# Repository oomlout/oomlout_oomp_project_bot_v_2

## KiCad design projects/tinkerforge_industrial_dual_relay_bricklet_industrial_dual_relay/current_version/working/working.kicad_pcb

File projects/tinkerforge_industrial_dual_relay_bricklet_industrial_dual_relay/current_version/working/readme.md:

# industrial_dual_relay_bricklet
 
## summary 
* id: tinkerforge_industrial_dual_relay_bricklet_industrial_dual_relay
* user: tinkerforge
* name: industrial_dual_relay_bricklet
* board: industrial_dual_relay
* repo: https://github.com/Tinkerforge/industrial-dual-relay-bricklet
* src_file_repo_kicad_pcb: hardware/industrial-dual-relay.kicad_pcb
* src_file_repo_kicad_pcb_link: https://github.com/Tinkerforge/industrial-dual-relay-bricklet/tree/master/hardware/industrial-dual-relay.kicad_pcb
* src_file_repo_kicad_sch: hardware/industrial-dual-relay.kicad_sch
* src_file_repo_kicad_sch_link: https://github.com/Tinkerforge/industrial-dual-relay-bricklet/tree/master/hardware/industrial-dual-relay.kicad_sch

* src_file_repo_sch: 
* src_file_repo_sch_link: https://github.com/Tinkerforge/industrial-dual-relay-bricklet/tree/master/
* full details link: https://github.com/oomlout/oomlout_oomp_project_bot_v_2/tree/main/projects/tinkerforge_industrial_dual_relay_bricklet_industrial_dual_relay/current_version/working

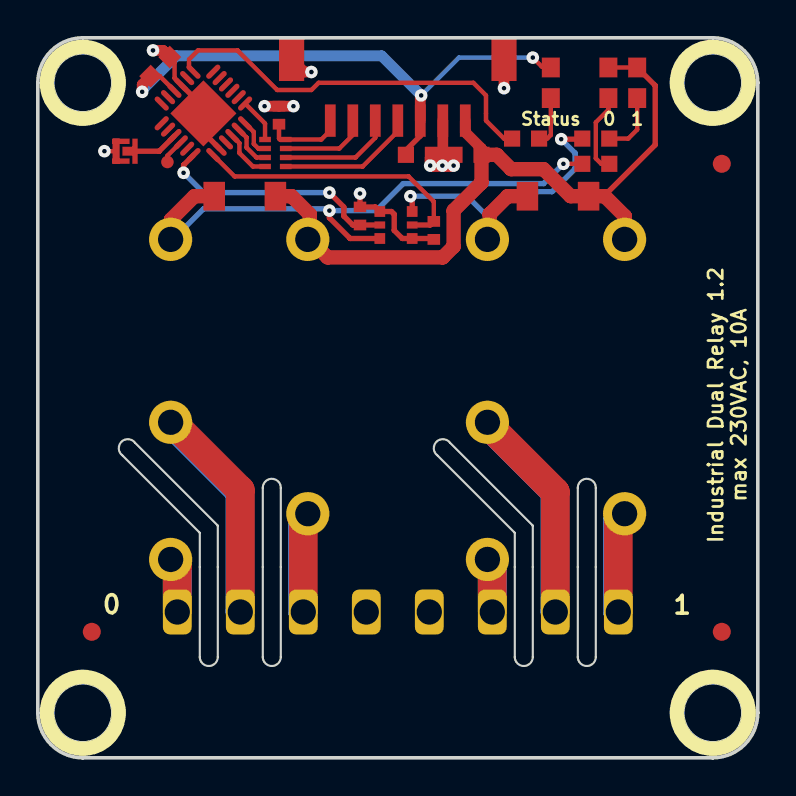
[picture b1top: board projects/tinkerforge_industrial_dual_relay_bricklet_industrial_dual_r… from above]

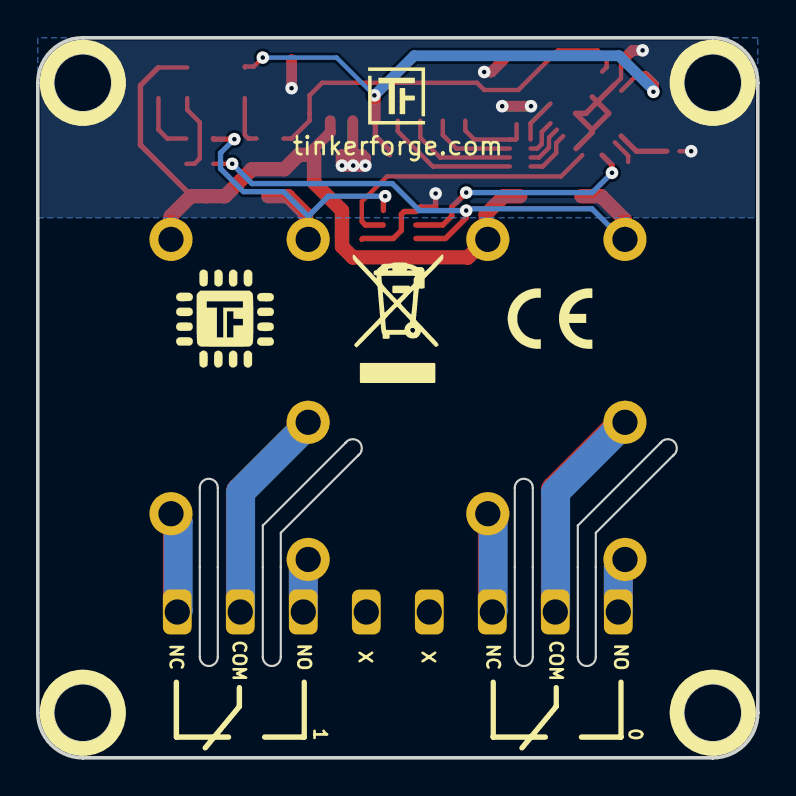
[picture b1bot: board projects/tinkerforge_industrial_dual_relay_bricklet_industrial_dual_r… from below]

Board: 2 copper layers, 40.0 x 40.0 mm, 31 parts (2 on the bottom side), 27 nets.

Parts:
C1, C3: 1uF; C0603F
C2: 220pF; C0402F
C4: 100nF; C0603F
D1, D2, D3: blue; D0603E
D4, D5: LL4148; MiniMelf
Fiducial_Mark: VAL**; Fiducial_Mark
Fiducial_Mark#2, Fiducial_Mark#3: VAL**; Fiducial_Mark
P1: CON-SENSOR2
P2: BOOT; SolderJumper
P3: CONN_8; OQ_8P_230V
P4: Debug; DEBUG_PAD
Q2, Q3: G5Q-1
R1, R2, R3: 1k; R0603F
R4, R5: 10k; R0402F
RP1: 82; 4X0402
U1: XMC1100; QFN24-4x4mm-0.5mm
U4, U5, U6: DRILL; DRILL_NP
VAL: CE_5mm
VAL#2: WEEE_7mm
locked: SSM6N7002KFU; SOT363

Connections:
+5V: C1.2, D2.1, D3.1, D4.2 (K), D5.2 (K), P1.1, Q2.A2, Q3.A2
GND: C1.1, C2.1, C3.1, C4.2, P1.2, P1.EP, P2.1, R4.1, R5.1, U1.9 (VSSP/VSS), U1.20 (P0.9_IO), U1.EXP (VSSP), locked.1, locked.4
unnamed: C2.2, P1.7, RP1.4
unnamed: D1.2, R1.2
unnamed: D2.2, R2.2
unnamed: D3.2, R3.2
unnamed: D4.1 (A), Q2.A1, R2.1, locked.6
unnamed: D5.1 (A), Q3.A1, R3.1, locked.3
unnamed: P1.4, RP1.1
unnamed: P1.5, RP1.2
unnamed: P1.6, RP1.3
unnamed: P2.2, U1.15 (P0.0_IO)
unnamed: P3.1, Q2.NO
unnamed: P3.2, Q2.COM
unnamed: P3.3, Q2.NC
unnamed: P3.6, Q3.NO
unnamed: P3.7, Q3.COM
unnamed: P3.8, Q3.NC
unnamed: P4.1, U1.16 (P0.5_IO)
unnamed: R1.1, U1.7 (P2.10_AIO)
RELAY0: R5.2, U1.19 (P0.8_IO), locked.5
RELAY1: R4.2, U1.18 (P0.7_IO), locked.2
S-CLK: RP1.7, U1.23 (P0.14_IO)
S-CS: RP1.8, U1.22 (P0.13_IO)
S-MISO: RP1.5, U1.1 (P2.0_AIO)
S-MOSI: RP1.6, U1.24 (P0.15_IO)
VCC: C3.2, C4.1, D1.1, P1.3, U1.10 (VDDP/VDD)

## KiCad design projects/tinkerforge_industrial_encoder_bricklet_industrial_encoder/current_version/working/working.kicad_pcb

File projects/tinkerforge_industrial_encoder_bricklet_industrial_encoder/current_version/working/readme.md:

# industrial_encoder_bricklet
 
## summary 
* id: tinkerforge_industrial_encoder_bricklet_industrial_encoder
* user: tinkerforge
* name: industrial_encoder_bricklet
* board: industrial_encoder
* repo: https://github.com/Tinkerforge/industrial-encoder-bricklet
* src_file_repo_kicad_pcb: hardware/industrial-encoder.kicad_pcb
* src_file_repo_kicad_pcb_link: https://github.com/Tinkerforge/industrial-encoder-bricklet/tree/master/hardware/industrial-encoder.kicad_pcb

* src_file_repo_sch: hardware/industrial-encoder.sch
* src_file_repo_sch_link: https://github.com/Tinkerforge/industrial-encoder-bricklet/tree/master/hardware/industrial-encoder.sch
* full details link: https://github.com/oomlout/oomlout_oomp_project_bot_v_2/tree/main/projects/tinkerforge_industrial_encoder_bricklet_industrial_encoder/current_version/working

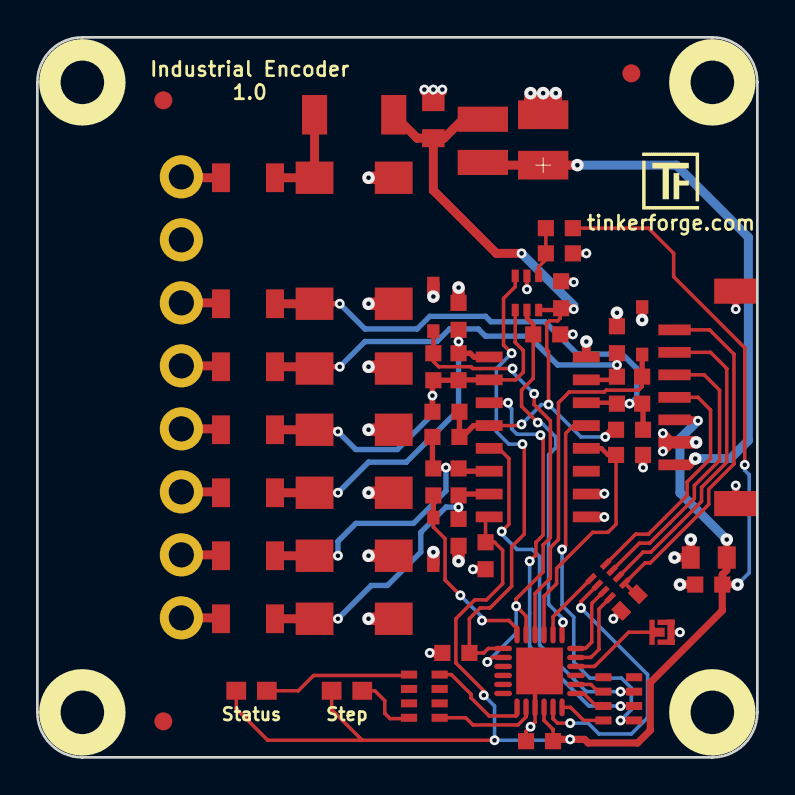
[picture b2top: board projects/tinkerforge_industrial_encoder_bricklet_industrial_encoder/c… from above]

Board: 2 copper layers, 40.0 x 40.0 mm, 63 parts (1 on the bottom side), 44 nets.

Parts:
C1: TBD; C0402E
C2: 10uF; C0805
C3, C5, C6: 100nF; C0603F
C4: 1uF; C0603F
C7: 100µF; 3528-21
C8: 10µF; C0805
D1: LED blue; D0603E
D2: LED green; D0603E
D3, D4, D11: ESD3V3D3B-TP; SOD-323
D5: PMEG6050; SOD-128
D6, D7, D8, D9, D10, D12, D13: SMAJ5.0CA; DO-214AC
Fiducial_Mark: VAL**; Fiducial_Mark
Fiducial_Mark#2, Fiducial_Mark#3: VAL**; Fiducial_Mark
L1: 6.8uH; WE-LQ-1210
P1: CON-SENSOR; CON-SENSOR2
P2: Boot; SolderJumper
P3: CONN_8; OQ_8P
R1, R2, R3, R4, R5, R8, R10, R11, R13, R22, R24: 1k; R0603F
R6, R7, R15: 100; R0603F
R9, R12, R23: 150; R0603F
R14, R16, R17, R18, R19, R20, R21: 10; R1206
RP1: TBD; 4X0402
RP2, RP3: 1k; 0603X4
U1: XMC1XXX24; QFN24-4x4mm-0.5mm
U2: OPA358; SC70-6
U3: ISL32173E; SOIC16
U4, U5, U6, U7: DRILL; DRILL_NP
VAL: CE_5mm

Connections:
+5V: C7.1, L1.1, P1.1
+5VA: C5.1, C8.2, D5.1, L1.2, R8.2, R11.2, R22.2, U2.6, U3.12
A-D: RP3.5, U3.5
A-T: D3.2, R6.1, U1.22
A/DAT: D7.1, R6.2, R8.1, R9.2, R16.2, U3.6
B-CLK: R1.2, U1.1, U2.3
B-CLK-EN: R2.2, U1.19, U2.5
B-D: RP3.6, U3.11
B-T: D4.2, R7.1, U1.2, U1.23
B/CLK: D9.1, R7.2, R11.1, R12.2, R18.2, U2.4, U3.10
EN-DIFF: R5.2, U1.21, U3.4
GND: C1.1, C2.1, C3.1, C4.1, C5.2, C6.2, C7.2, C8.1, D3.1, D4.1, D6.2, D7.2, D8.2, D9.2, D10.2, D11.1, D12.2, D13.2, P1.2, P1.EP, P2.1, P3.2, R1.1, R2.1, R4.1, R5.1, R10.1, R13.1, R24.1, U1.9, U1.EXP, U2.2, U3.1, U3.2, U3.8
I: D12.1, R15.2, R20.2, R22.1, R23.2, U3.14
I-D: RP3.7, U3.13
I-T: D11.2, R15.1, U1.24
unnamed: C1.2, P1.7, RP1.5
unnamed: D1.2, RP2.1
unnamed: D2.2, RP2.4
unnamed: D5.2, D6.1, R14.2
unnamed: P1.4, RP1.8
unnamed: P1.5, RP1.7
unnamed: P1.6, RP1.6
unnamed: P2.2, U1.16
unnamed: P3.1, R14.1
unnamed: P3.3, R16.1
unnamed: P3.4, R17.1
unnamed: P3.5, R18.1
unnamed: P3.6, R19.1
unnamed: P3.7, R20.1
unnamed: P3.8, R21.1
unnamed: R3.1, R4.2, U2.1
unnamed: RP2.5, U1.8
unnamed: RP2.8, U1.7
unnamed: RP3.2, U1.14
unnamed: RP3.3, U1.13
unnamed: RP3.4, U1.12
S-CLK: RP1.2, U1.11
S-CS: RP1.1, U1.20
S-MISO: RP1.4, U1.17
S-MOSI: RP1.3, U1.18
VCC: C2.2, C3.2, C4.2, C6.1, D1.1, D2.1, P1.3, R3.2, U1.10, U3.16
~A: D8.1, R9.1, R10.2, R17.2, U3.7
~B: D10.1, R12.1, R13.2, R19.2, U3.9
~I: D13.1, R21.2, R23.1, R24.2, U3.15

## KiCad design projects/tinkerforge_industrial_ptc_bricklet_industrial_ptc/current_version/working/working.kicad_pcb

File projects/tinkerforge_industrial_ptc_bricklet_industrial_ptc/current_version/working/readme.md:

# industrial_ptc_bricklet
 
## summary 
* id: tinkerforge_industrial_ptc_bricklet_industrial_ptc
* user: tinkerforge
* name: industrial_ptc_bricklet
* board: industrial_ptc
* repo: https://github.com/Tinkerforge/industrial-ptc-bricklet
* src_file_repo_kicad_pcb: hardware/industrial-ptc.kicad_pcb
* src_file_repo_kicad_pcb_link: https://github.com/Tinkerforge/industrial-ptc-bricklet/tree/master/hardware/industrial-ptc.kicad_pcb
* src_file_repo_kicad_sch: hardware/industrial-ptc.kicad_sch
* src_file_repo_kicad_sch_link: https://github.com/Tinkerforge/industrial-ptc-bricklet/tree/master/hardware/industrial-ptc.kicad_sch

* src_file_repo_sch: 
* src_file_repo_sch_link: https://github.com/Tinkerforge/industrial-ptc-bricklet/tree/master/
* full details link: https://github.com/oomlout/oomlout_oomp_project_bot_v_2/tree/main/projects/tinkerforge_industrial_ptc_bricklet_industrial_ptc/current_version/working

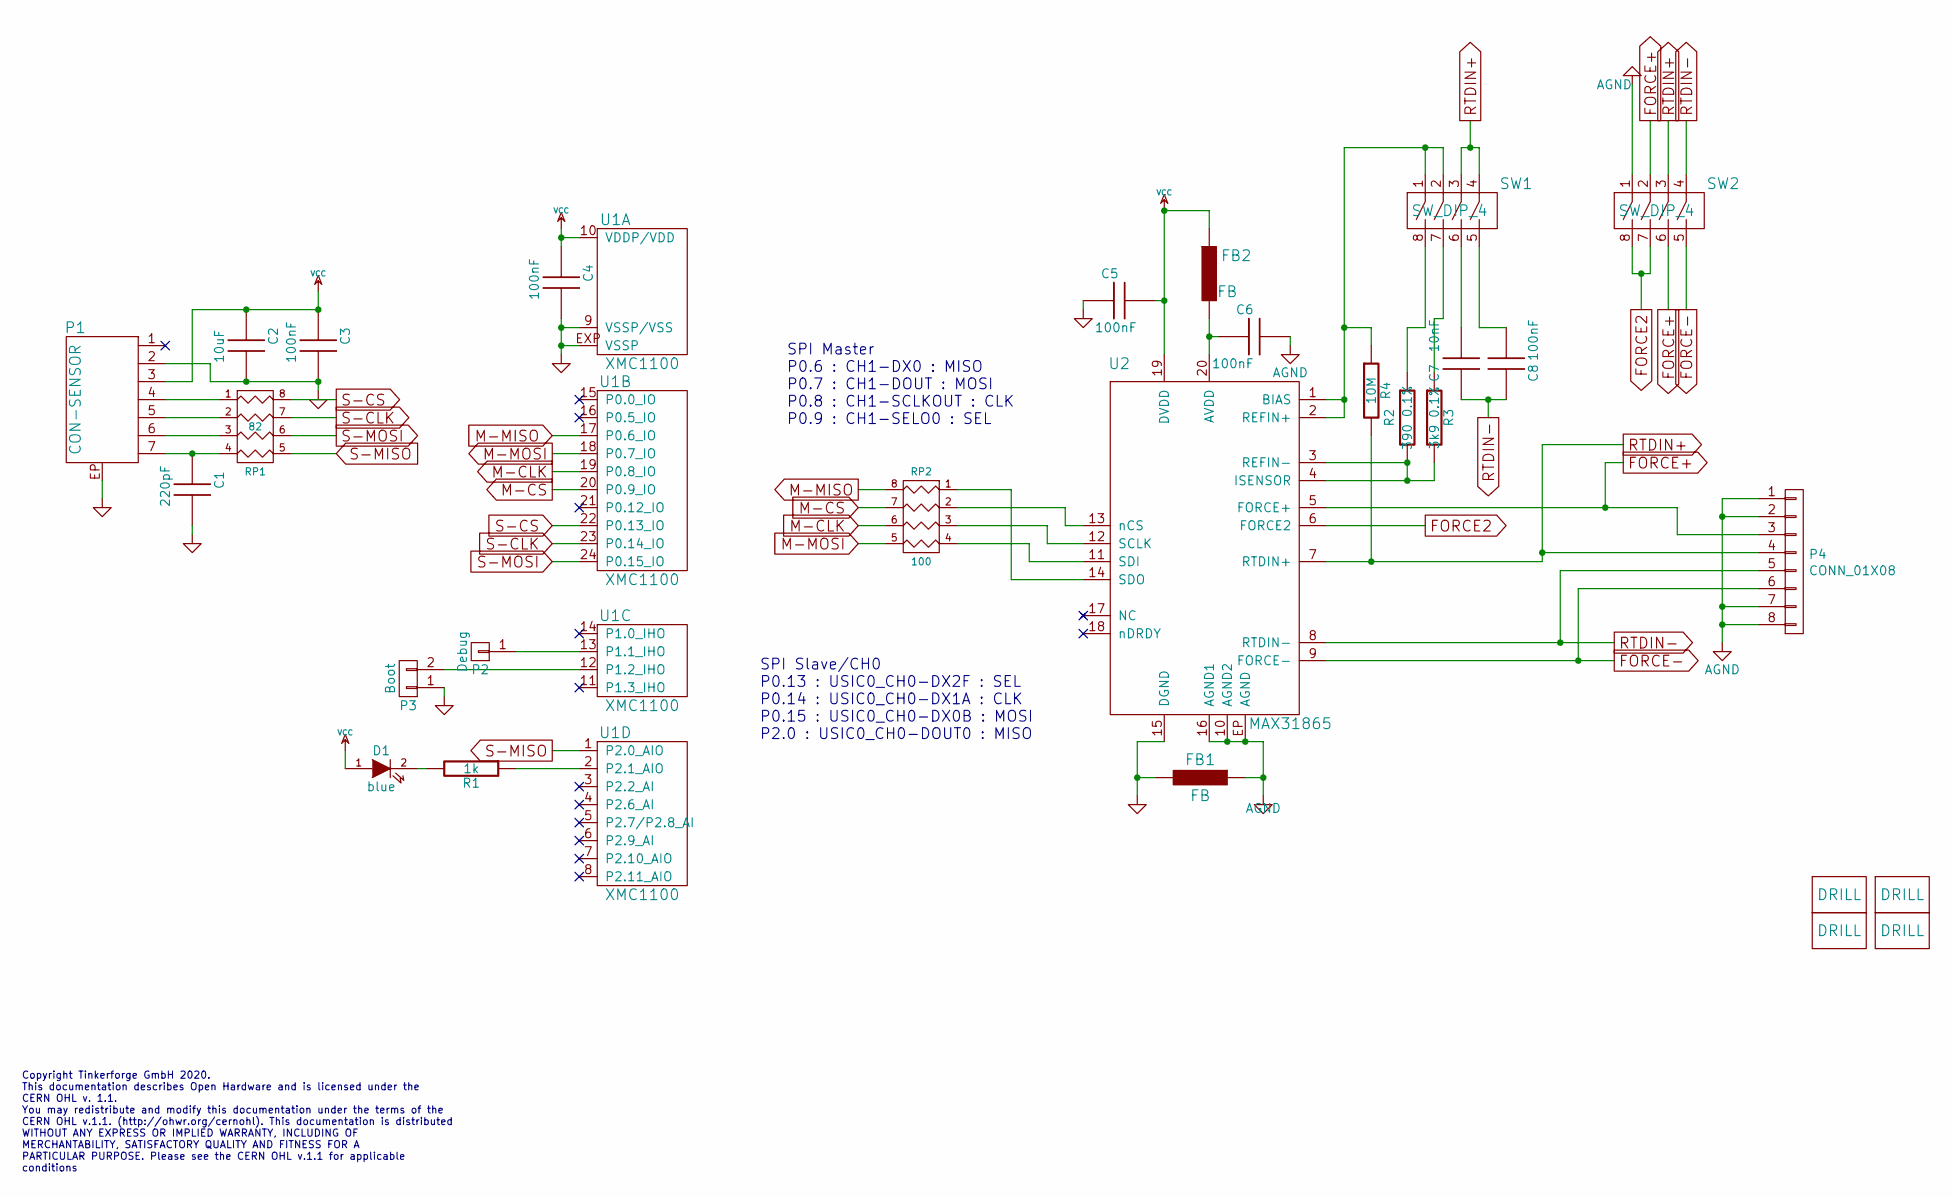
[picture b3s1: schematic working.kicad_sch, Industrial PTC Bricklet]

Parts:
C1: 220pF; C0402F
C2: 10uF; C0805
C3, C4, C5, C6, C8: 100nF; C0603F
C7: 10nF; C0603F
D1: blue; D0603F
FB1, FB2: FB; R0603F
P1: CON-SENSOR; CON-SENSOR2
P2: Debug; DEBUG_PAD
P3: Boot; SolderJumper
P4: CONN_01X08; OQ_8P
R1: 1k; R0603F
R2: 390 0.1%; R0603F
R3: 3k9 0.1%; R0603F
R4: 10M; R0603F
RP1: 82; 4X0402
RP2: 100; 0603X4
SW1, SW2: SW_DIP_4; SW_DIP_4_THT
U1: XMC1100; QFN24-4x4mm-0.5mm
U2: MAX31865; QFN-20-5x5
U3, U4, U5, U6: DRILL; DRILL_NP

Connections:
AGND: C6.2, FB1.1, P4.1, P4.2, P4.7, P4.8, SW2.1, U2.10 (AGND2), U2.16 (AGND1), U2.EP (AGND)
FORCE2: SW2.7, SW2.8, U2.6 (FORCE2)
FORCE+: P4.3, SW2.2, SW2.6, U2.5 (FORCE+)
FORCE-: P4.6, SW2.5, U2.9 (FORCE-)
GND: C1.2, C2.2, C3.2, C4.2, C5.1, FB1.2, P1.2, P1.EP, P3.1, U1.9 (VSSP/VSS), U1.EXP (VSSP), U2.15 (DGND)
M-CLK: RP2.6 (R3), U1.19 (P0.8_IO)
M-CS: RP2.7 (R2), U1.20 (P0.9_IO)
M-MISO: RP2.8 (R1), U1.17 (P0.6_IO)
M-MOSI: RP2.5 (R4), U1.18 (P0.7_IO)
unnamed: C1.1, P1.7, RP1.4
unnamed: C6.1, FB2.2, U2.20 (AVDD)
unnamed: C7.2, SW1.6
unnamed: C8.2, SW1.5
unnamed: D1.2 (K), R1.2
unnamed: P1.4, RP1.1
unnamed: P1.5, RP1.2
unnamed: P1.6, RP1.3
unnamed: P2.1, U1.13 (P1.1_IHO)
unnamed: P3.2, U1.12 (P1.2_IHO)
unnamed: R1.1, U1.2 (P2.1_AIO)
unnamed: R2.1, SW1.8
unnamed: R2.2, R3.2, U2.3 (REFIN-), U2.4 (ISENSOR)
unnamed: R3.1, SW1.7
unnamed: R4.1, SW1.1, SW1.2, U2.1 (BIAS), U2.2 (REFIN+)
unnamed: RP2.1, U2.14 (SDO)
unnamed: RP2.2, U2.13 (nCS)
unnamed: RP2.3, U2.12 (SCLK)
unnamed: RP2.4, U2.11 (SDI)
RTDIN+: P4.4, R4.2, SW1.3, SW1.4, SW2.3, U2.7 (RTDIN+)
RTDIN-: C7.1, C8.1, P4.5, SW2.4, U2.8 (RTDIN-)
S-CLK: RP1.7 (R2), U1.23 (P0.14_IO)
S-CS: RP1.8 (R1), U1.22 (P0.13_IO)
S-MISO: RP1.5 (R4), U1.1 (P2.0_AIO)
S-MOSI: RP1.6 (R3), U1.24 (P0.15_IO)
VCC: C2.1, C3.1, C4.1, C5.2, D1.1 (A), FB2.1, P1.3, U1.10 (VDDP/VDD), U2.19 (DVDD)

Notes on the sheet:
SPI Master P0.6 : CH1-DX0 : MISO P0.7 : CH1-DOUT : MOSI P0.8 : CH1-SCLKOUT : CLK P0.9 : CH1-SELO0 : SEL
Copyright Tinkerforge GmbH 2020. This documentation describes Open Hardware and is licensed under the CERN OHL v. 1.1. You may redistribute and modify this documentation under the terms of the CERN OHL v.1.1. (http://ohwr.org/cernohl). This documentation is distributed WITHOUT ANY EXPRESS OR IMPLIE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
SPI Slave/CH0 P0.13 : USIC0_CH0-DX2F : SEL P0.14 : USIC0_CH0-DX1A : CLK P0.15 : USIC0_CH0-DX0B : MOSI P2.0 : USIC0_CH0-DOUT0 : MISO

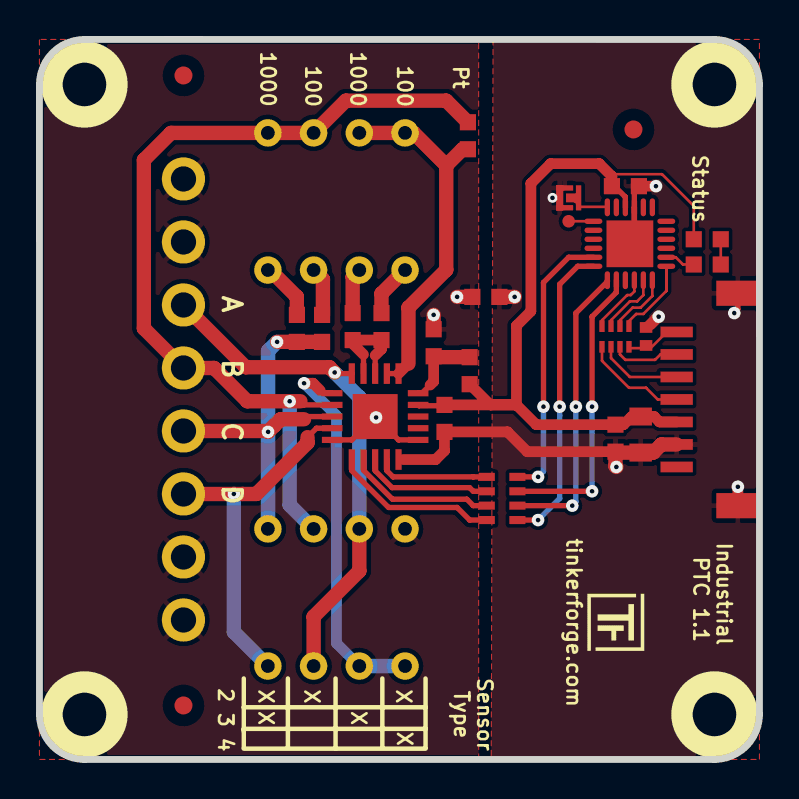
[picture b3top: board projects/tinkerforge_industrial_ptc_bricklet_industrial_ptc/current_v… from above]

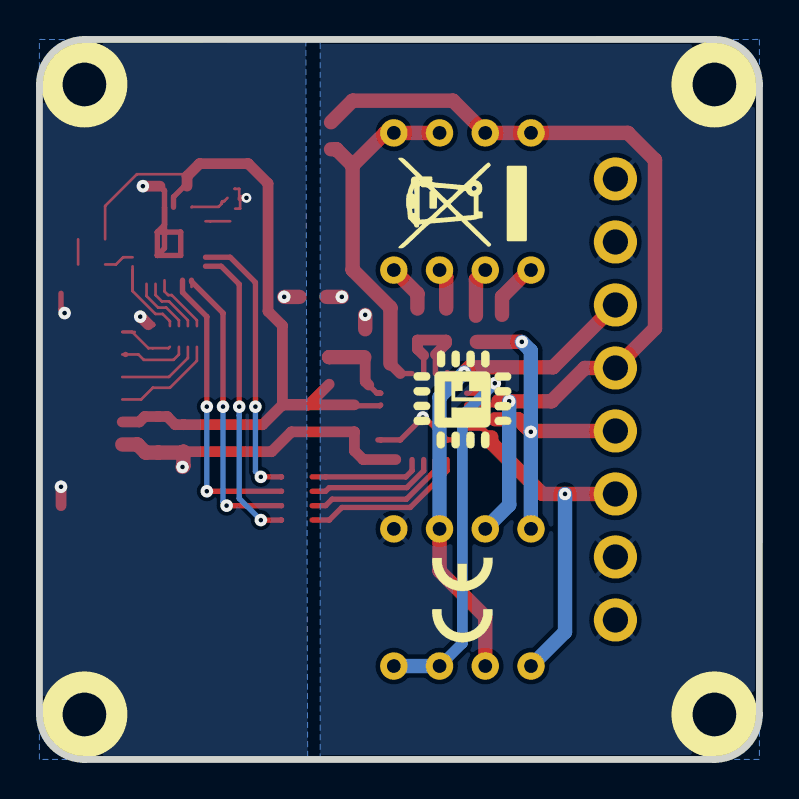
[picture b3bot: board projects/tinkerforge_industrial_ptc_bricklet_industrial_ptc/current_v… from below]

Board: 2 copper layers, 40.0 x 40.0 mm, 34 parts (2 on the bottom side), 35 nets.

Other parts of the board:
Fiducial_Mark: VAL**; Fiducial_Mark
Fiducial_Mark#2, Fiducial_Mark#3: VAL**; Fiducial_Mark
VAL: CE_5mm
VAL#2: WEEE_7mm

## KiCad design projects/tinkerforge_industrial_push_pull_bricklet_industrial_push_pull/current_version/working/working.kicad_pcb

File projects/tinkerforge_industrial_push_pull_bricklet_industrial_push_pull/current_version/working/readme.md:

# industrial_push_pull_bricklet
 
## summary 
* id: tinkerforge_industrial_push_pull_bricklet_industrial_push_pull
* user: tinkerforge
* name: industrial_push_pull_bricklet
* board: industrial_push_pull
* repo: https://github.com/Tinkerforge/industrial-push-pull-bricklet
* src_file_repo_kicad_pcb: hardware/industrial-push-pull.kicad_pcb
* src_file_repo_kicad_pcb_link: https://github.com/Tinkerforge/industrial-push-pull-bricklet/tree/master/hardware/industrial-push-pull.kicad_pcb

* src_file_repo_sch: hardware/industrial-push-pull.sch
* src_file_repo_sch_link: https://github.com/Tinkerforge/industrial-push-pull-bricklet/tree/master/hardware/industrial-push-pull.sch
* full details link: https://github.com/oomlout/oomlout_oomp_project_bot_v_2/tree/main/projects/tinkerforge_industrial_push_pull_bricklet_industrial_push_pull/current_version/working

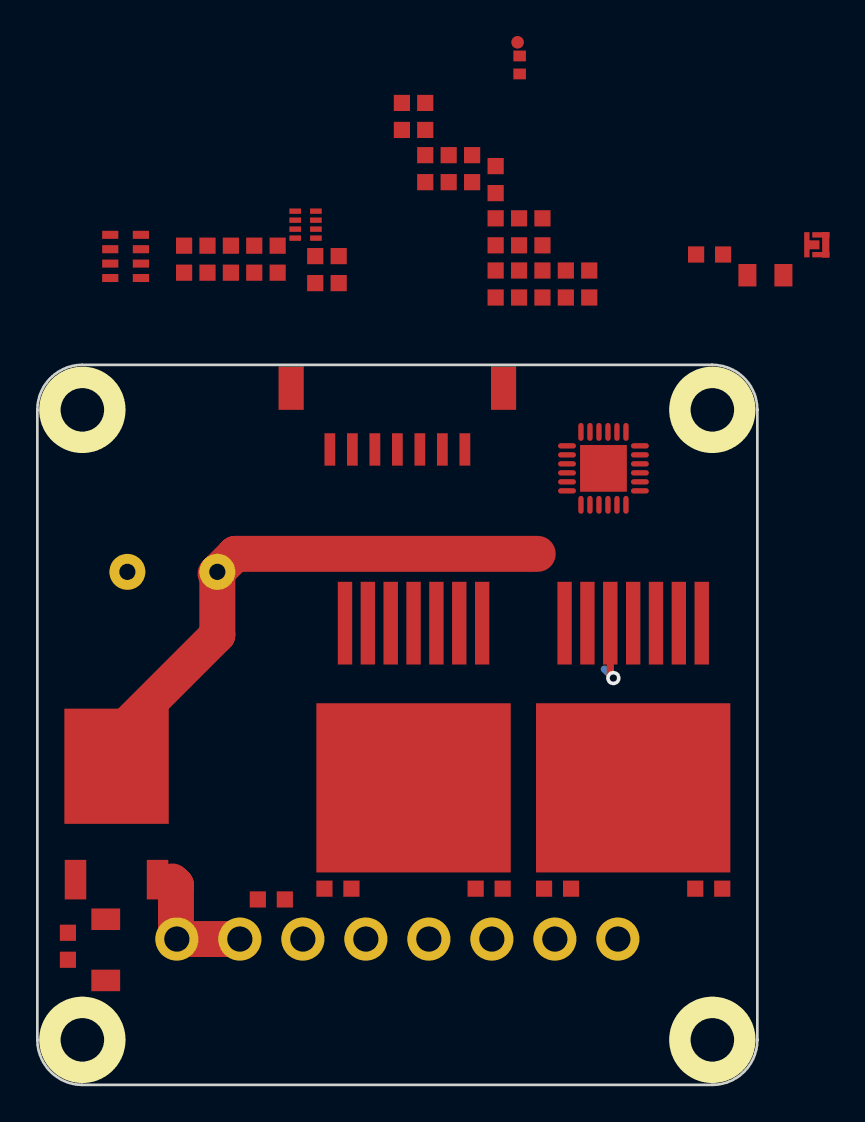
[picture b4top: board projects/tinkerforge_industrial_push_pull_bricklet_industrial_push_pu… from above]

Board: 2 copper layers, 40.0 x 40.0 mm, 46 parts (0 on the bottom side), 37 nets.

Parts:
10k1: R; R0603F
C1, C4, C6, C7, C8: 100nF; C0603F
C2: 220pF; C0402F
C3: 10uF; C0805
C5: 1nF; C0603F
C9: 1000uF 35V; ELKO_RAD_12
C10, C11, C12: 100nF 100V; C0603F
C13, C14, C15, C16: 220nF 100V; C0603F
D1: blue STATUS; D0603F
D2: 10V; MiniMelf
D3: red FAIL; D0603F
D4: green CH1; D0603F
D5: green CH2; D0603F
P1: CON-SENSOR; CON-SENSOR2
P2: Digital Output; OQ_8P
P3: Debug; DEBUG_PAD
P4: Boot; SolderJumper
Q1: MOSFET; TO-252-3
R1: 1k; R0603F
R2: 510; C0603F
R3, R4: 510; R0603F
R6, R7, R8, R9, R10: 10k; R0603F
R11: 91k; R0603F
RP1: 1k; 4X0603
RP2: 82; 4X0402
U1: XMC1100; QFN24-4x4mm-0.5mm
U2, U3: IFX007T; TO263-7
U6, U7, U8, U9: DRILL; DRILL_NP

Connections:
3V3: C1.1, C3.1, C4.1, D1.1, D3.1, D4.1, D5.1, P1.3, U1.10
+VSW: C9.1, C10.1, C11.1, C13.1, C15.1, D2.2, Q1.D, R11.1, U2.7, U3.7
GND: 10k1.2, C1.2, C2.2, C3.2, C4.2, C5.2, C6.2, C7.2, C8.2, C9.2, C10.2, C11.2, C12.2, C14.2, C16.2, P1.2, P1.EP, P2.3, P2.4, P4.1, Q1.G, R1.2, R2.2, R3.2, R4.2, R10.2, U1.9, U1.EXP, U2.1, U3.1
IN1: R6.2, U1.15
IN2: R8.2, U1.16
INH: R7.2, R9.2, U1.17
IS1: C5.1, R1.1, U1.14, U2.6
IS2: C7.1, R3.1, U1.13, U3.6
unnamed: 10k1.1, D2.1
unnamed: C2.1, P1.7, RP2.4
unnamed: C6.1, R2.1, U2.5
unnamed: C8.1, R4.1, U3.5
unnamed: C12.1, P2.1, P2.2, Q1.S
unnamed: C13.2, C14.1, P2.5, P2.6, U2.4, U2.8
unnamed: C15.2, C16.1, P2.7, P2.8, U3.4, U3.8
unnamed: D1.2, RP1.4
unnamed: D3.2, RP1.1
unnamed: D4.2, RP1.2
unnamed: D5.2, RP1.3
unnamed: P1.4, RP2.1
unnamed: P1.5, RP2.2
unnamed: P1.6, RP2.3
unnamed: P3.1, U1.19
unnamed: P4.2, U1.18
unnamed: R6.1, U2.2
unnamed: R7.1, U2.3
unnamed: R8.1, U3.2
unnamed: R9.1, U3.3
unnamed: RP1.5, U1.7
unnamed: RP1.6, U1.11
unnamed: RP1.7, U1.12
unnamed: RP1.8, U1.21
S-CLK: RP2.7, U1.23
S-CS: RP2.8, U1.22
S-MISO: RP2.5, U1.1
S-MOSI: RP2.6, U1.24
VIN: R10.1, R11.2, U1.2

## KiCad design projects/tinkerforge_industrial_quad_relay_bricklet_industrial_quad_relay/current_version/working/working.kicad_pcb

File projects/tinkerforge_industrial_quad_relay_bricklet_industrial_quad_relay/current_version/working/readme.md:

# industrial_quad_relay_bricklet
 
## summary 
* id: tinkerforge_industrial_quad_relay_bricklet_industrial_quad_relay
* user: tinkerforge
* name: industrial_quad_relay_bricklet
* board: industrial_quad_relay
* repo: https://github.com/Tinkerforge/industrial-quad-relay-bricklet
* src_file_repo_kicad_pcb: hardware/industrial-quad-relay.kicad_pcb
* src_file_repo_kicad_pcb_link: https://github.com/Tinkerforge/industrial-quad-relay-bricklet/tree/master/hardware/industrial-quad-relay.kicad_pcb

* src_file_repo_sch: hardware/industrial-quad-relay.sch
* src_file_repo_sch_link: https://github.com/Tinkerforge/industrial-quad-relay-bricklet/tree/master/hardware/industrial-quad-relay.sch
* full details link: https://github.com/oomlout/oomlout_oomp_project_bot_v_2/tree/main/projects/tinkerforge_industrial_quad_relay_bricklet_industrial_quad_relay/current_version/working

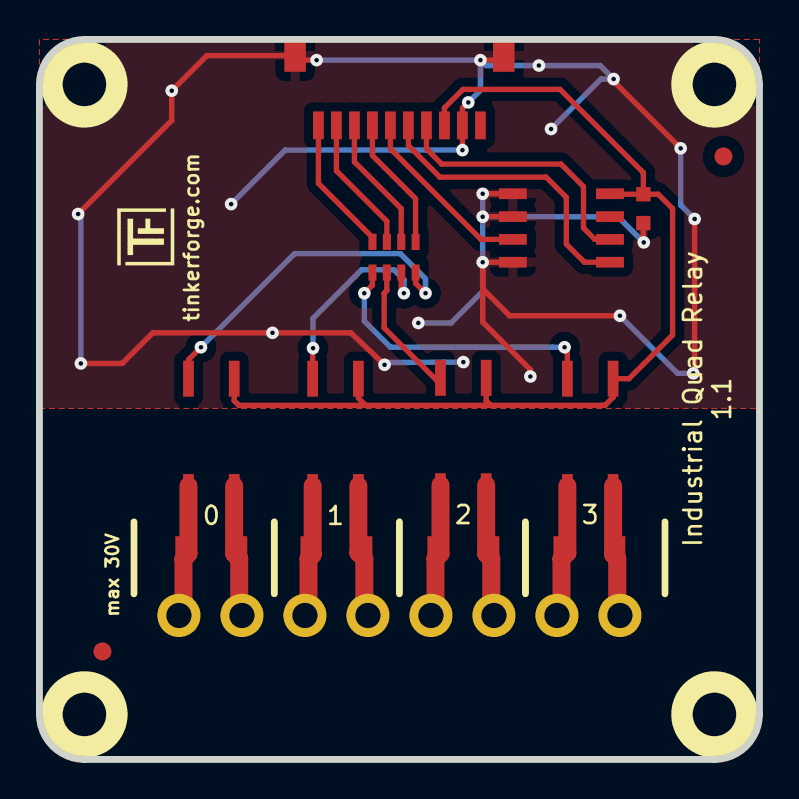
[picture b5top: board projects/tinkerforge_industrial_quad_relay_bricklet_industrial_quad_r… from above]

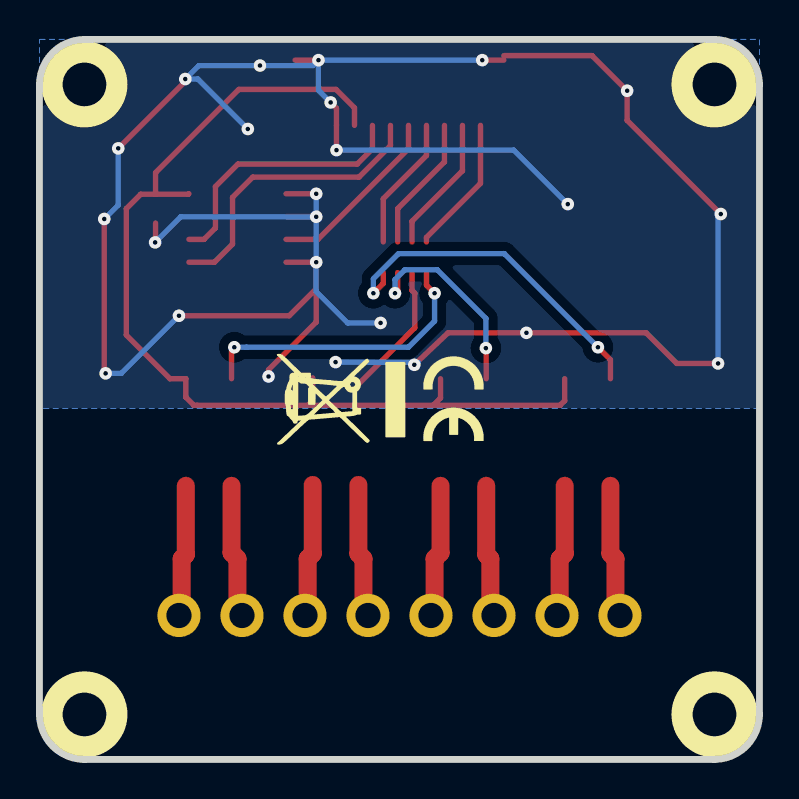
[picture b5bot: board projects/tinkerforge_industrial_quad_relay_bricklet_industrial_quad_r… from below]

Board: 2 copper layers, 40.0 x 40.0 mm, 21 parts (2 on the bottom side), 21 nets.

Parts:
C1: 100nF; C0603
Fiducial_Mark: VAL**; Fiducial_Mark
Fiducial_Mark#2: VAL**; Fiducial_Mark
P1: CON-SENSOR
P2: Digital Output; OQ_8P
R1, R2, R3, R4: VJ13PC0300KBA; R1210
RP1: 1k; 0603X4
U1: M24C64; SOIC8
U2, U3, U4, U5: CPC1020N; SOP4-WIDE
U6, U7, U8, U9: DRILL; DRILL_NP
VAL: WEEE_7mm
VAL#2: CE_5mm

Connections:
3V3: C1.1, P1.3, U1.8, U2.1, U3.1, U4.1, U5.1
GND: C1.2, P1.2, P1.EP, U1.1, U1.2, U1.4
unnamed: P1.4, U1.6
unnamed: P1.5, U1.5
unnamed: P1.6, U1.3
unnamed: P2.1, R1.1, U2.3
unnamed: P2.2, R1.2, U2.4
unnamed: P2.3, R2.1, U3.3
unnamed: P2.4, R2.2, U3.4
unnamed: P2.5, R3.1, U4.3
unnamed: P2.6, R3.2, U4.4
unnamed: P2.7, R4.1, U5.3
unnamed: P2.8, R4.2, U5.4
unnamed: RP1.5, U5.2
unnamed: RP1.6, U4.2
unnamed: RP1.7, U3.2
unnamed: RP1.8, U2.2
OUTPUT1: P1.7, RP1.1
OUTPUT2: P1.8, RP1.2
OUTPUT3: P1.9, RP1.3
OUTPUT4: P1.10, RP1.4

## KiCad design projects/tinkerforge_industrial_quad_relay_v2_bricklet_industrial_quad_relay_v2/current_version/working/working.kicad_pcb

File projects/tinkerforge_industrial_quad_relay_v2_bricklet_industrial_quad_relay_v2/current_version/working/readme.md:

# industrial_quad_relay_v2_bricklet
 
## summary 
* id: tinkerforge_industrial_quad_relay_v2_bricklet_industrial_quad_relay_v2
* user: tinkerforge
* name: industrial_quad_relay_v2_bricklet
* board: industrial_quad_relay_v2
* repo: https://github.com/Tinkerforge/industrial-quad-relay-v2-bricklet
* src_file_repo_kicad_pcb: hardware/industrial-quad-relay-v2.kicad_pcb
* src_file_repo_kicad_pcb_link: https://github.com/Tinkerforge/industrial-quad-relay-v2-bricklet/tree/master/hardware/industrial-quad-relay-v2.kicad_pcb
* src_file_repo_kicad_sch: hardware/industrial-quad-relay-v2.kicad_sch
* src_file_repo_kicad_sch_link: https://github.com/Tinkerforge/industrial-quad-relay-v2-bricklet/tree/master/hardware/industrial-quad-relay-v2.kicad_sch

* src_file_repo_sch: 
* src_file_repo_sch_link: https://github.com/Tinkerforge/industrial-quad-relay-v2-bricklet/tree/master/
* full details link: https://github.com/oomlout/oomlout_oomp_project_bot_v_2/tree/main/projects/tinkerforge_industrial_quad_relay_v2_bricklet_industrial_quad_relay_v2/current_version/working

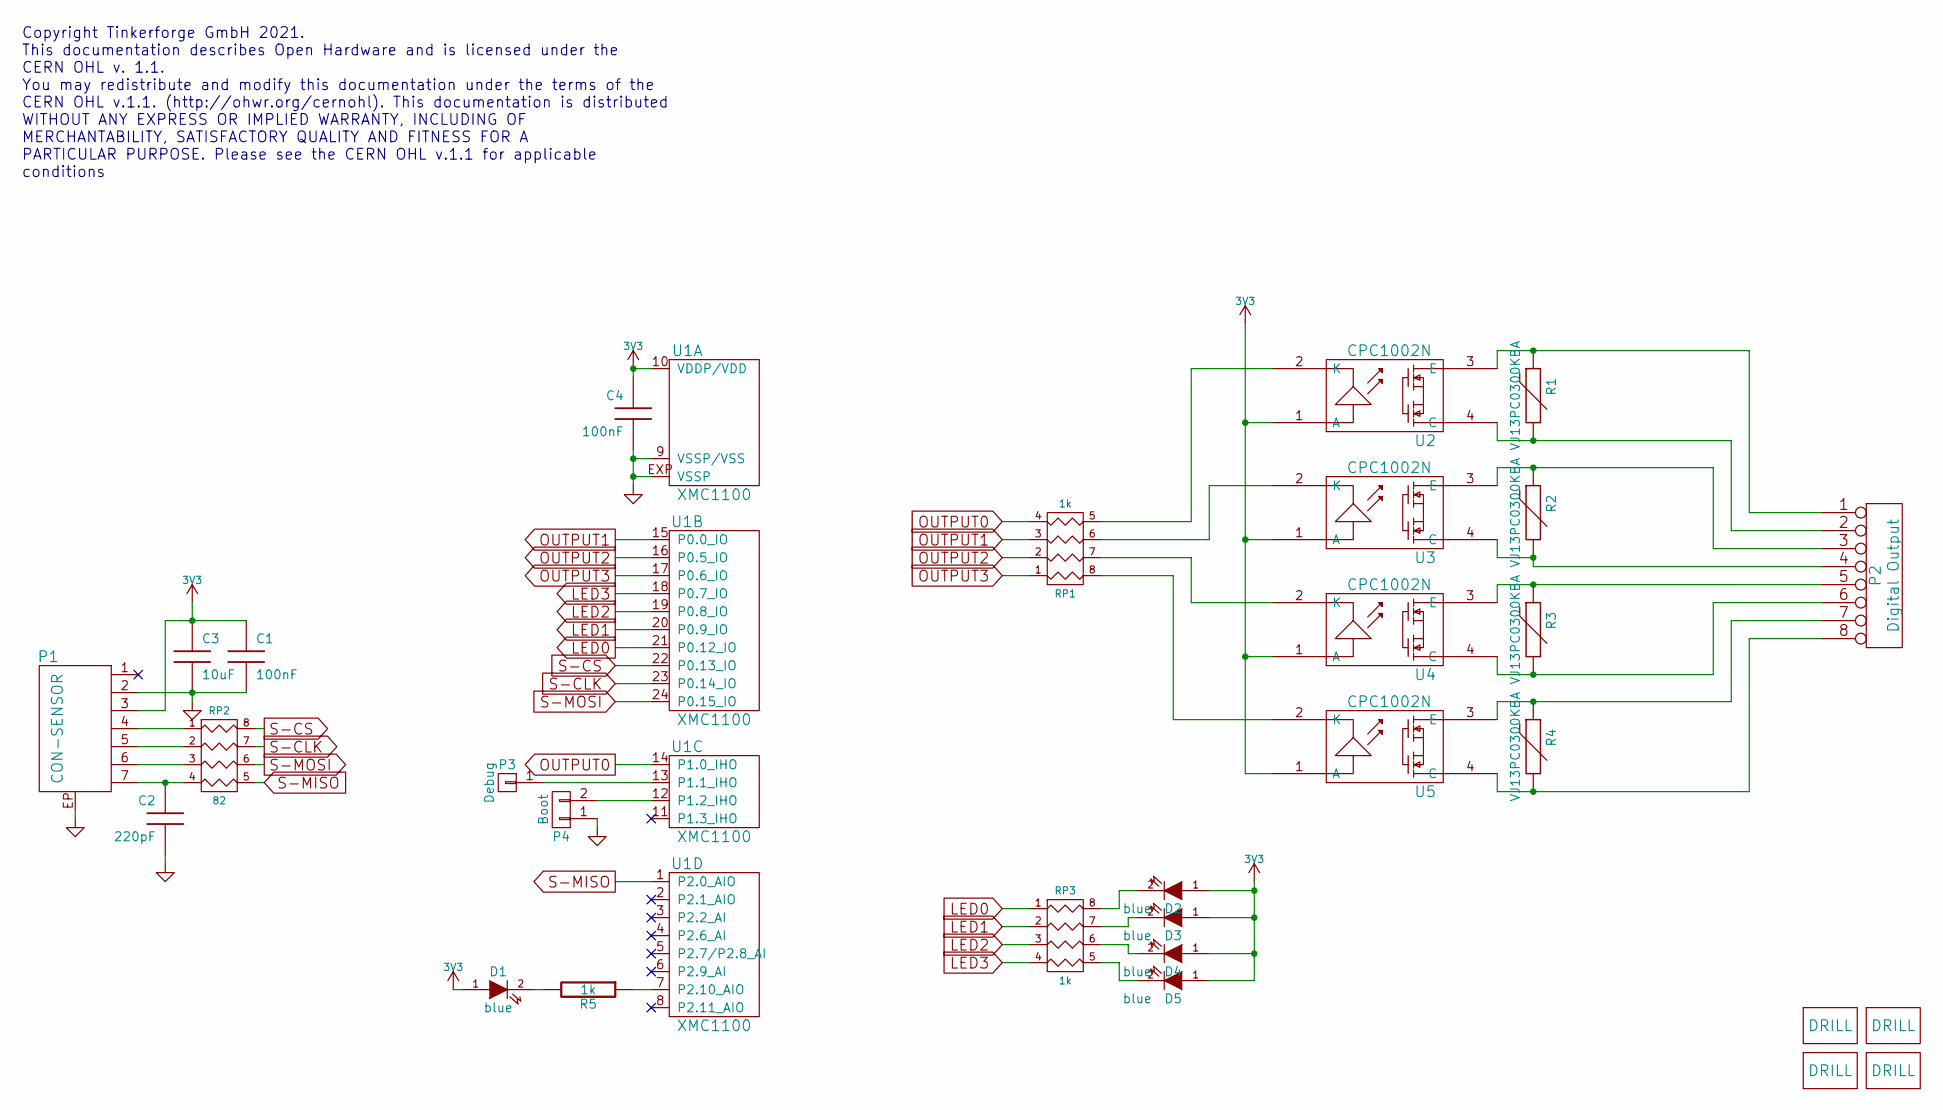
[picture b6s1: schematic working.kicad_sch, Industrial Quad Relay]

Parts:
C1, C4: 100nF; C0603F
C2: 220pF; C0402F
C3: 10uF; C0805
D1, D2, D3, D4, D5: blue; D0603F
P1: CON-SENSOR; CON-SENSOR2
P2: Digital Output; OQ_8P
P3: Debug; DEBUG_PAD
P4: Boot; SolderJumper
R1, R2, R3, R4: VJ13PC0300KBA; R1210
R5: 1k; R0603F
RP1, RP3: 1k; 0603X4
RP2: 82; 4X0402
U1: XMC1100; QFN24-4x4mm-0.5mm
U2, U3, U4, U5: CPC1002N; SOP4-WIDE
U6, U7, U8, U9: DRILL; DRILL_NP

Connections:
3V3: C1.1, C3.1, C4.1, D1.1 (A), D2.1 (A), D3.1 (A), D4.1 (A), D5.1 (A), P1.3, U1.10 (VDDP/VDD), U2.1 (A), U3.1 (A), U4.1 (A), U5.1 (A)
GND: C1.2, C2.2, C3.2, C4.2, P1.2, P1.EP, P4.1, U1.9 (VSSP/VSS), U1.EXP (VSSP)
LED0: RP3.1, U1.21 (P0.12_IO)
LED1: RP3.2, U1.20 (P0.9_IO)
LED2: RP3.3, U1.19 (P0.8_IO)
LED3: RP3.4, U1.18 (P0.7_IO)
unnamed: C2.1, P1.7, RP2.4
unnamed: D1.2 (K), R5.2
unnamed: D2.2 (K), RP3.8 (R1)
unnamed: D3.2 (K), RP3.7 (R2)
unnamed: D4.2 (K), RP3.6 (R3)
unnamed: D5.2 (K), RP3.5 (R4)
unnamed: P1.4, RP2.1
unnamed: P1.5, RP2.2
unnamed: P1.6, RP2.3
unnamed: P2.1, R1.1, U2.3 (E)
unnamed: P2.2, R1.2, U2.4 (C)
unnamed: P2.3, R2.1, U3.3 (E)
unnamed: P2.4, R2.2, U3.4 (C)
unnamed: P2.5, R3.1, U4.3 (E)
unnamed: P2.6, R3.2, U4.4 (C)
unnamed: P2.7, R4.1, U5.3 (E)
unnamed: P2.8, R4.2, U5.4 (C)
unnamed: P3.1, U1.13 (P1.1_IHO)
unnamed: P4.2, U1.12 (P1.2_IHO)
unnamed: R5.1, U1.7 (P2.10_AIO)
unnamed: RP1.5 (R4), U2.2 (K)
unnamed: RP1.6 (R3), U3.2 (K)
unnamed: RP1.7 (R2), U4.2 (K)
unnamed: RP1.8 (R1), U5.2 (K)
OUTPUT0: RP1.4, U1.14 (P1.0_IHO)
OUTPUT1: RP1.3, U1.15 (P0.0_IO)
OUTPUT2: RP1.2, U1.16 (P0.5_IO)
OUTPUT3: RP1.1, U1.17 (P0.6_IO)
S-CLK: RP2.7 (R2), U1.23 (P0.14_IO)
S-CS: RP2.8 (R1), U1.22 (P0.13_IO)
S-MISO: RP2.5 (R4), U1.1 (P2.0_AIO)
S-MOSI: RP2.6 (R3), U1.24 (P0.15_IO)

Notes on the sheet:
Copyright Tinkerforge GmbH 2021. This documentation describes Open Hardware and is licensed under the CERN OHL v. 1.1. You may redistribute and modify this documentation under the terms of the CERN OHL v.1.1. (http://ohwr.org/cernohl). This documentation is distributed WITHOUT ANY EXPRESS OR IMPLIE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

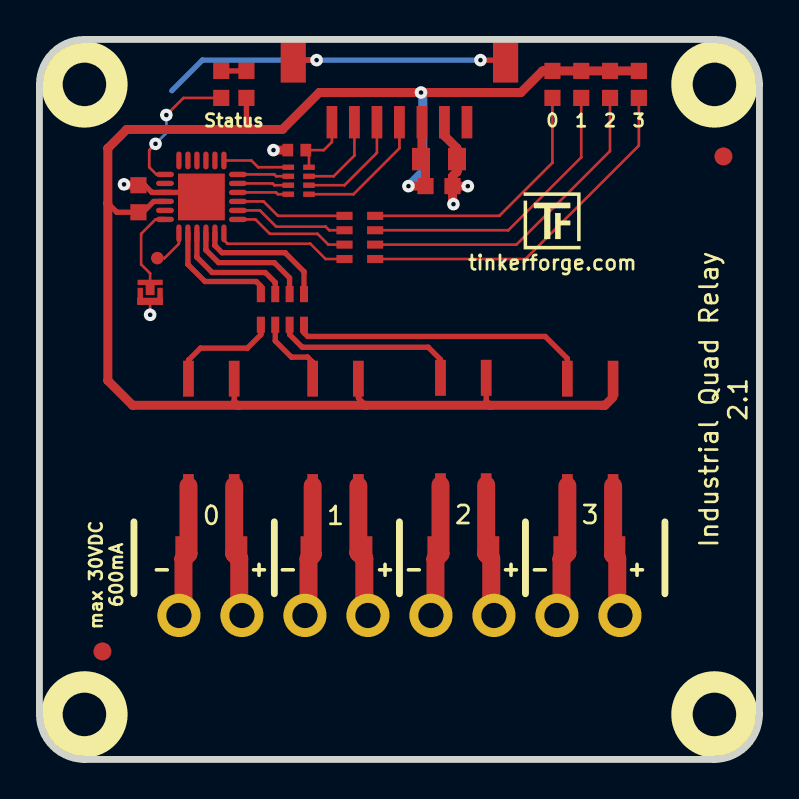
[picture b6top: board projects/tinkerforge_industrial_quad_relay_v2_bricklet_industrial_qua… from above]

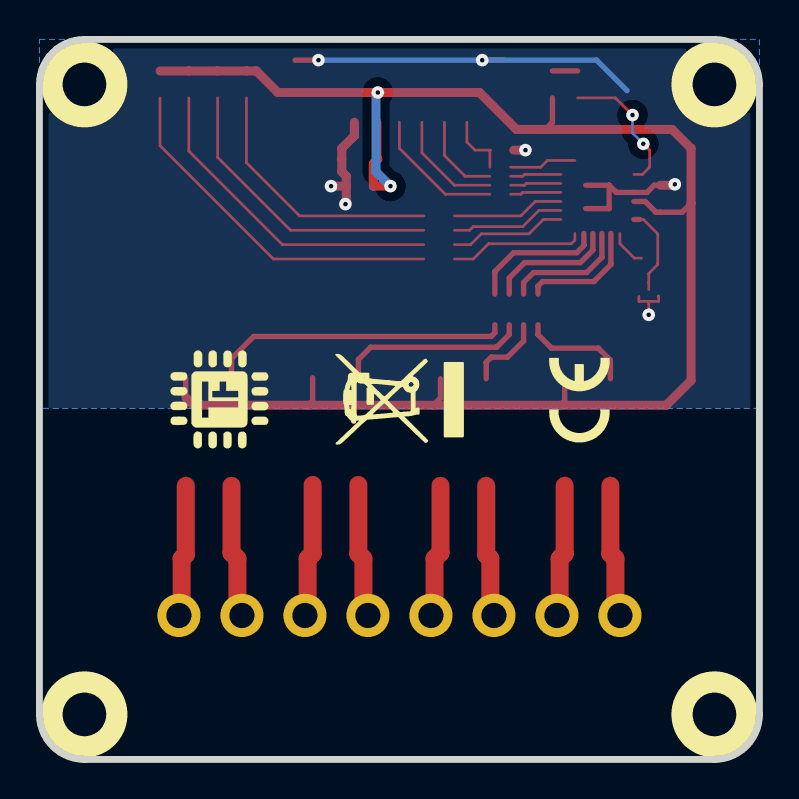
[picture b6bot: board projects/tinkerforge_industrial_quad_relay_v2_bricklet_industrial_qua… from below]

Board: 2 copper layers, 40.0 x 40.0 mm, 34 parts (2 on the bottom side), 38 nets.

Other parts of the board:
Fiducial_Mark: VAL**; Fiducial_Mark
Fiducial_Mark#2: VAL**; Fiducial_Mark
VAL: WEEE_7mm
VAL#2: CE_5mm

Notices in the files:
projects/tinkerforge_industrial_dual_relay_bricklet_industrial_dual_relay/current_version/working/working.kicad_pcb:
Licensed under CERN OHL v.1.1
Copyright (©) 2023, B.Nordmeyer
Copyright Tinkerforge GmbH 2023.
projects/tinkerforge_industrial_encoder_bricklet_industrial_encoder/current_version/working/working.kicad_pcb:
Copyright (©) 2017, B.Nordmeyer
Copyright Tinkerforge GmbH 2017.
projects/tinkerforge_industrial_ptc_bricklet_industrial_ptc/current_version/working/working.kicad_pcb:
Copyright (©) 2020, T.Schneidermann
